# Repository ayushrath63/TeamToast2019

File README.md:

Team Toast - Micromouse 2018-2019
======
Created by Ayush Rath and Emily Chen

Hardware (PCB) and software used to build and program a Micromouse robot

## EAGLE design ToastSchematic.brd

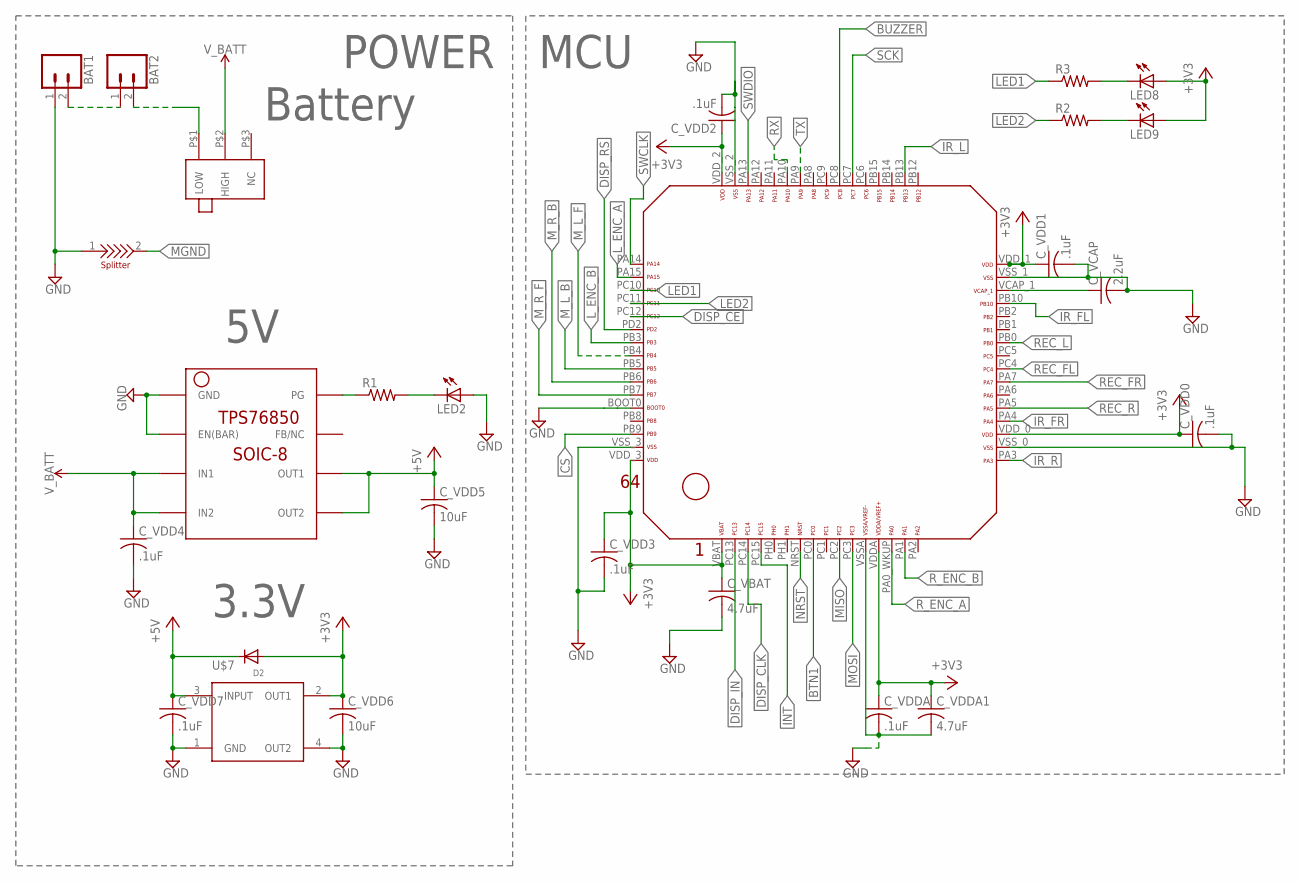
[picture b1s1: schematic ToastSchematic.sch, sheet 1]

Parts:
BAT1, BAT2: CONN_02JST-PTH-2; JST-2-PTH
C_VBAT: 4.7uF; C0603
C_VCAP: 2.2uF; C0603
C_VDD0, C_VDD1, C_VDD2, C_VDD3, C_VDD4, C_VDD7: .1uF; C0603
C_VDD5, C_VDD6: 10uF; C0603
C_VDDA: .1uF; C0603
C_VDDA1: 4.7uF; C0603
D2: DIODESOD-323F; SOD-323F
LED2, LED8, LED9: LEDCHIPLED_0603; CHIPLED_0603
R1, R2, R3: R-US_R0603; R0603
U$1: STM32F411/446_LQFP64
U$2: GH39P0
U$3: TPS76850(SOIC-8)
U$7: TLV1117; SOT-223
U$9: SPLITTER

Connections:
+3V3: C_VBAT.1, C_VDD0.1, C_VDD1.1, C_VDD2.1, C_VDD3.1, C_VDD6.1, C_VDDA.1, C_VDDA1.1, D2.A, LED8.A, LED9.A, U$1.VBAT, U$1.VDDA, U$1.VDD_0, U$1.VDD_1, U$1.VDD_2, U$1.VDD_3, U$7.2 (OUT1); also elsewhere on the board
+5V: C_VDD5.1, C_VDD7.1, D2.C, U$3.OUT1, U$3.OUT2, U$7.3 (INPUT); also elsewhere on the board
BTN1: U$1.PC0; also elsewhere on the board
BUZZER: U$1.PC8; also elsewhere on the board
CS: U$1.PB9; also elsewhere on the board
DISP_CE: U$1.PC12; also elsewhere on the board
DISP_CLK: U$1.PC14; also elsewhere on the board
DISP_IN: U$1.PC13; also elsewhere on the board
DISP_RS: U$1.PD2; also elsewhere on the board
GND: BAT1.1, C_VBAT.2, C_VCAP.2, C_VDD0.2, C_VDD1.2, C_VDD2.2, C_VDD3.2, C_VDD4.2, C_VDD5.2, C_VDD6.2, C_VDD7.2, C_VDDA.2, C_VDDA1.2, LED2.A, U$1.BOOT0, U$1.VSSA, U$1.VSS_0, U$1.VSS_1, U$1.VSS_2, U$1.VSS_3, U$3.EN(BAR), U$3.GND, U$7.1 (GND), U$7.4 (OUT2), U$9.1; also elsewhere on the board
INT: U$1.PC15; also elsewhere on the board
IR_FL: U$1.PB10; also elsewhere on the board
IR_FR: U$1.PA4; also elsewhere on the board
IR_L: U$1.PB13; also elsewhere on the board
IR_R: U$1.PA3; also elsewhere on the board
LED1: R3.1, U$1.PC10
LED2: R2.1, U$1.PC11
L_ENC_A: U$1.PA15; also elsewhere on the board
L_ENC_B: U$1.PB3; also elsewhere on the board
MGND: U$9.2; also elsewhere on the board
MISO: U$1.PC2; also elsewhere on the board
MOSI: U$1.PC3; also elsewhere on the board
M_L_B: U$1.PB5; also elsewhere on the board
M_L_F: U$1.PB4; also elsewhere on the board
M_R_B: U$1.PB6; also elsewhere on the board
M_R_F: U$1.PB7; also elsewhere on the board
unnamed: BAT1.2, BAT2.1
unnamed: BAT2.2, U$2.P$1 (LOW)
unnamed: C_VCAP.1, U$1.VCAP_1
unnamed: LED8.C, R3.2
unnamed: LED2.C, R1.2
unnamed: R1.1, U$3.PG
unnamed: LED9.C, R2.2
NRST: U$1.NRST; also elsewhere on the board
REC_FL: U$1.PC4; also elsewhere on the board
REC_FR: U$1.PA7; also elsewhere on the board
REC_L: U$1.PB0; also elsewhere on the board
REC_R: U$1.PA5; also elsewhere on the board
RX: U$1.PA10; also elsewhere on the board
R_ENC_A: U$1.PA0_WKUP (PA0_AKUP); also elsewhere on the board
R_ENC_B: U$1.PA1; also elsewhere on the board
SCK: U$1.PC7; also elsewhere on the board
SWCLK: U$1.PA14; also elsewhere on the board
SWDIO: U$1.PA13; also elsewhere on the board
TX: U$1.PA9; also elsewhere on the board
V_BATT: C_VDD4.1, U$2.P$2 (HIGH), U$3.IN1, U$3.IN2; also elsewhere on the board

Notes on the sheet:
MCU
POWER
3.3V
Battery

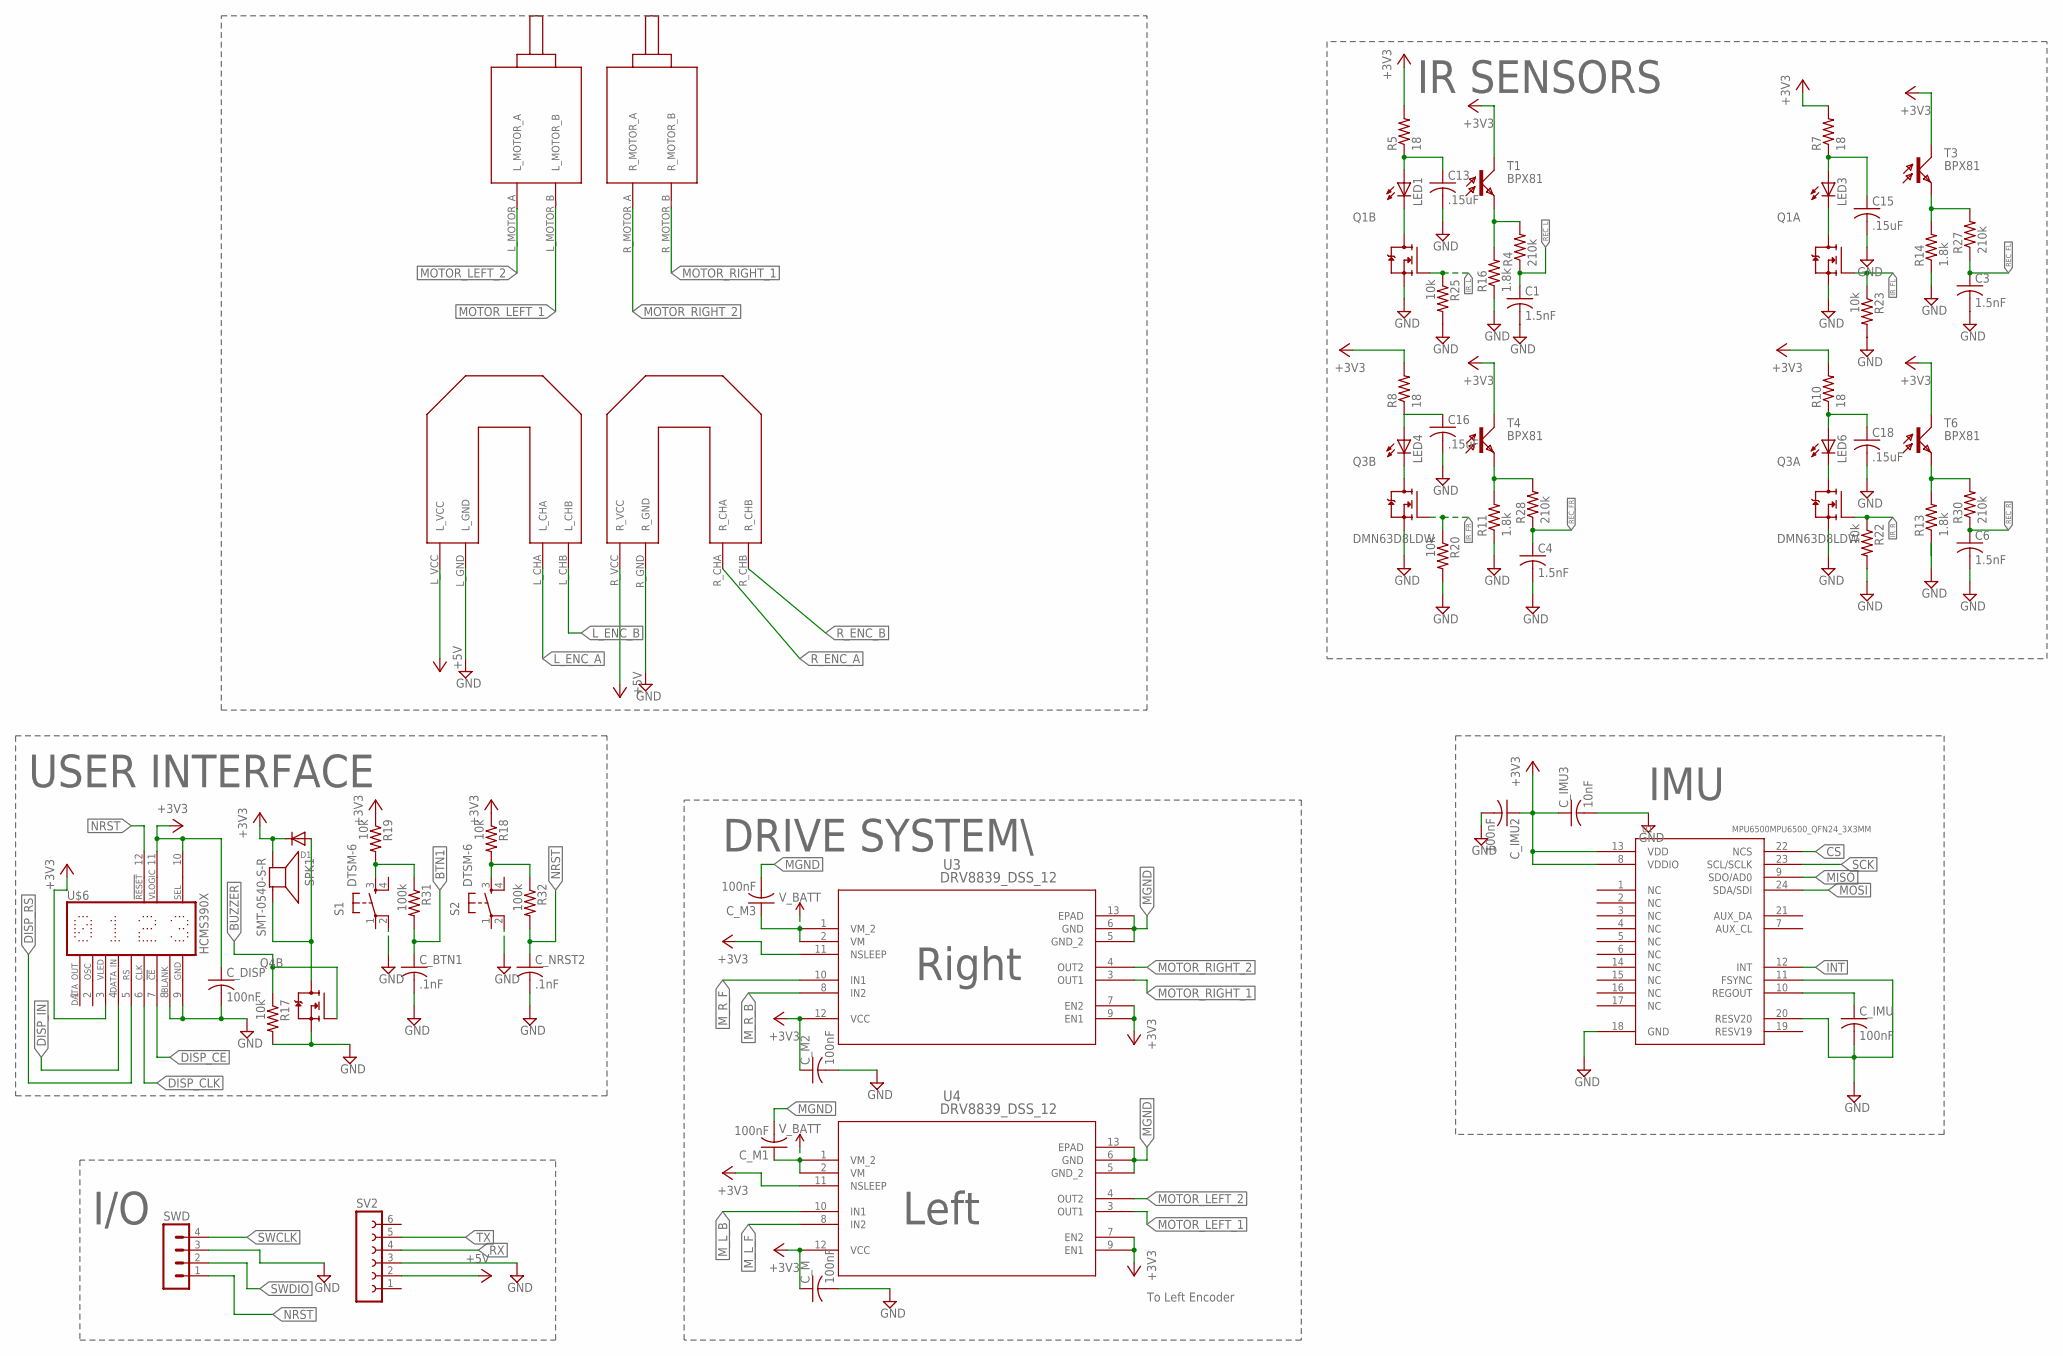
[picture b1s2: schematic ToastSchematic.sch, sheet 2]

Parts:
C1, C3, C4, C6: 1.5nF; C0603K
C13, C15, C16, C18: .15uF; C0603K
C_BTN1: .1nF; C0603K
C_DISP: 100nF; C0603K
C_IMU, C_IMU2: 100nF; C0603K
C_IMU3: 10nF; C0603K
C_M, C_M1, C_M2, C_M3: 100nF; C0603K
C_NRST2: .1nF; C0603K
D1: DIODESOD-323F; SOD-323F
LED1, LED3, LED4, LED6: LED5MM
Q1, Q3, Q4: DMN63D8LDW; SOT363
R4, R27, R28, R30: 210k; R0603
R5, R7, R8, R10: 18; R0603
R11, R13, R14, R16: 1.8k; R0603
R17, R18, R19, R20, R22, R23, R25: 10k; R0603
R31, R32: 100k; R0603
S1, S2: DTSM-6
SPK1: SMT-0540-S-R
SV2: FE06-1; FE06
SWD: MA04-1
T1, T3, T4, T6: BPX81
U1: MPU6500MPU6500_QFN24_3X3MM; QFN24_3X3MM
U3, U4: DRV8839_DSS_12; DSS12_P9X2
U$4: FUTURA_V1.0_MOTOR_MOUNT; FUTURA_V1.0_MOTOT_MOUNT
U$6: HCMS390X

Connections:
+3V3: C_DISP.1, C_IMU2.1, C_IMU3.1, C_M.1, C_M2.1, D1.C, R5.2, R7.2, R8.2, R10.2, R18.1, R19.1, SPK1.- (+), T1.C, T3.C, T4.C, T6.C, U1.8 (VDDIO), U1.13 (VDD), U3.7 (EN2), U3.9 (EN1), U3.11 (NSLEEP), U3.12 (VCC), U4.7 (EN2), U4.9 (EN1), U4.11 (NSLEEP), U4.12 (VCC), U$6.3 (VLED), U$6.10 (SEL), U$6.11 (VLOGIC); also elsewhere on the board
+5V: SV2.2, U$4.L_VCC, U$4.R_VCC; also elsewhere on the board
BTN1: C_BTN1.1, R31.2; also elsewhere on the board
BUZZER: Q4.5 (G), R17.1; also elsewhere on the board
CS: U1.22 (NCS); also elsewhere on the board
DISP_CE: U$6.7 (!CE); also elsewhere on the board
DISP_CLK: U$6.6 (CLK); also elsewhere on the board
DISP_IN: U$6.4 (IN); also elsewhere on the board
DISP_RS: U$6.5 (RS); also elsewhere on the board
GND: C1.2, C3.2, C4.2, C6.2, C13.2, C15.2, C16.2, C18.2, C_BTN1.2, C_DISP.2, C_IMU.2, C_IMU2.2, C_IMU3.2, C_M.2, C_M2.2, C_NRST2.2, Q1.1 (S), Q1.4 (S), Q3.1 (S), Q3.4 (S), Q4.4 (S), R11.1, R13.1, R14.1, R16.1, R17.2, R20.2, R22.2, R23.2, R25.2, S1.2, S2.2, SV2.3, SWD.3, U1.11 (FSYNC), U1.18 (GND), U1.20 (RESV20), U$4.L_GND, U$4.R_GND, U$6.8 (BLANK), U$6.9 (GND); also elsewhere on the board
INT: U1.12 (INT); also elsewhere on the board
IR_FL: Q1.2 (G), R23.1; also elsewhere on the board
IR_FR: Q3.5 (G), R20.1; also elsewhere on the board
IR_L: Q1.5 (G), R25.1; also elsewhere on the board
IR_R: Q3.2 (G), R22.1; also elsewhere on the board
L_ENC_A: U$4.L_CHA; also elsewhere on the board
L_ENC_B: U$4.L_CHB; also elsewhere on the board
MGND: C_M1.2, C_M3.2, U3.5 (GND_2), U3.6 (GND), U3.13 (EPAD), U4.5 (GND_2), U4.6 (GND), U4.13 (EPAD); also elsewhere on the board
MISO: U1.9 (SDO/AD0); also elsewhere on the board
MOSI: U1.24 (SDA/SDI); also elsewhere on the board
MOTOR_LEFT_1: U4.3 (OUT1), U$4.L_MOTOR_B
MOTOR_LEFT_2: U4.4 (OUT2), U$4.L_MOTOR_A
MOTOR_RIGHT_1: U3.3 (OUT1), U$4.R_MOTOR_B
MOTOR_RIGHT_2: U3.4 (OUT2), U$4.R_MOTOR_A
M_L_B: U4.10 (IN1); also elsewhere on the board
M_L_F: U4.8 (IN2); also elsewhere on the board
M_R_B: U3.8 (IN2); also elsewhere on the board
M_R_F: U3.10 (IN1); also elsewhere on the board
unnamed: C13.1, LED1.A, R5.1
unnamed: LED1.K (C), Q1.3 (D)
unnamed: R19.2, R31.1, S1.3
unnamed: LED3.K (C), Q1.6 (D)
unnamed: R18.2, R32.1, S2.3
unnamed: C18.1, LED6.A, R10.1
unnamed: LED6.K (C), Q3.6 (D)
unnamed: C16.1, LED4.A, R8.1
unnamed: C_IMU.1, U1.10 (REGOUT)
unnamed: LED4.K (C), Q3.3 (D)
unnamed: D1.A, Q4.3 (D), SPK1.+ (-)
unnamed: R4.2, R16.2, T1.E
unnamed: R14.2, R27.2, T3.E
unnamed: R11.2, R28.2, T4.E
unnamed: R13.2, R30.2, T6.E
unnamed: C15.1, LED3.A, R7.1
NRST: C_NRST2.1, R32.2, SWD.1, U$6.12 (NOT_RESET); also elsewhere on the board
REC_FL: C3.1, R27.1; also elsewhere on the board
REC_FR: C4.1, R28.1; also elsewhere on the board
REC_L: C1.1, R4.1; also elsewhere on the board
REC_R: C6.1, R30.1; also elsewhere on the board
RX: SV2.4; also elsewhere on the board
R_ENC_A: U$4.R_CHA; also elsewhere on the board
R_ENC_B: U$4.R_CHB; also elsewhere on the board
SCK: U1.23 (SCL/SCLK); also elsewhere on the board
SWCLK: SWD.4; also elsewhere on the board
SWDIO: SWD.2; also elsewhere on the board
TX: SV2.5; also elsewhere on the board
V_BATT: C_M1.1, C_M3.1, U3.1 (VM_2), U3.2 (VM), U4.1 (VM_2), U4.2 (VM); also elsewhere on the board

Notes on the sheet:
DRIVE SYSTEM\
Right
Left
USER INTERFACE
IR SENSORS
IMU
I/O
To Left Encoder

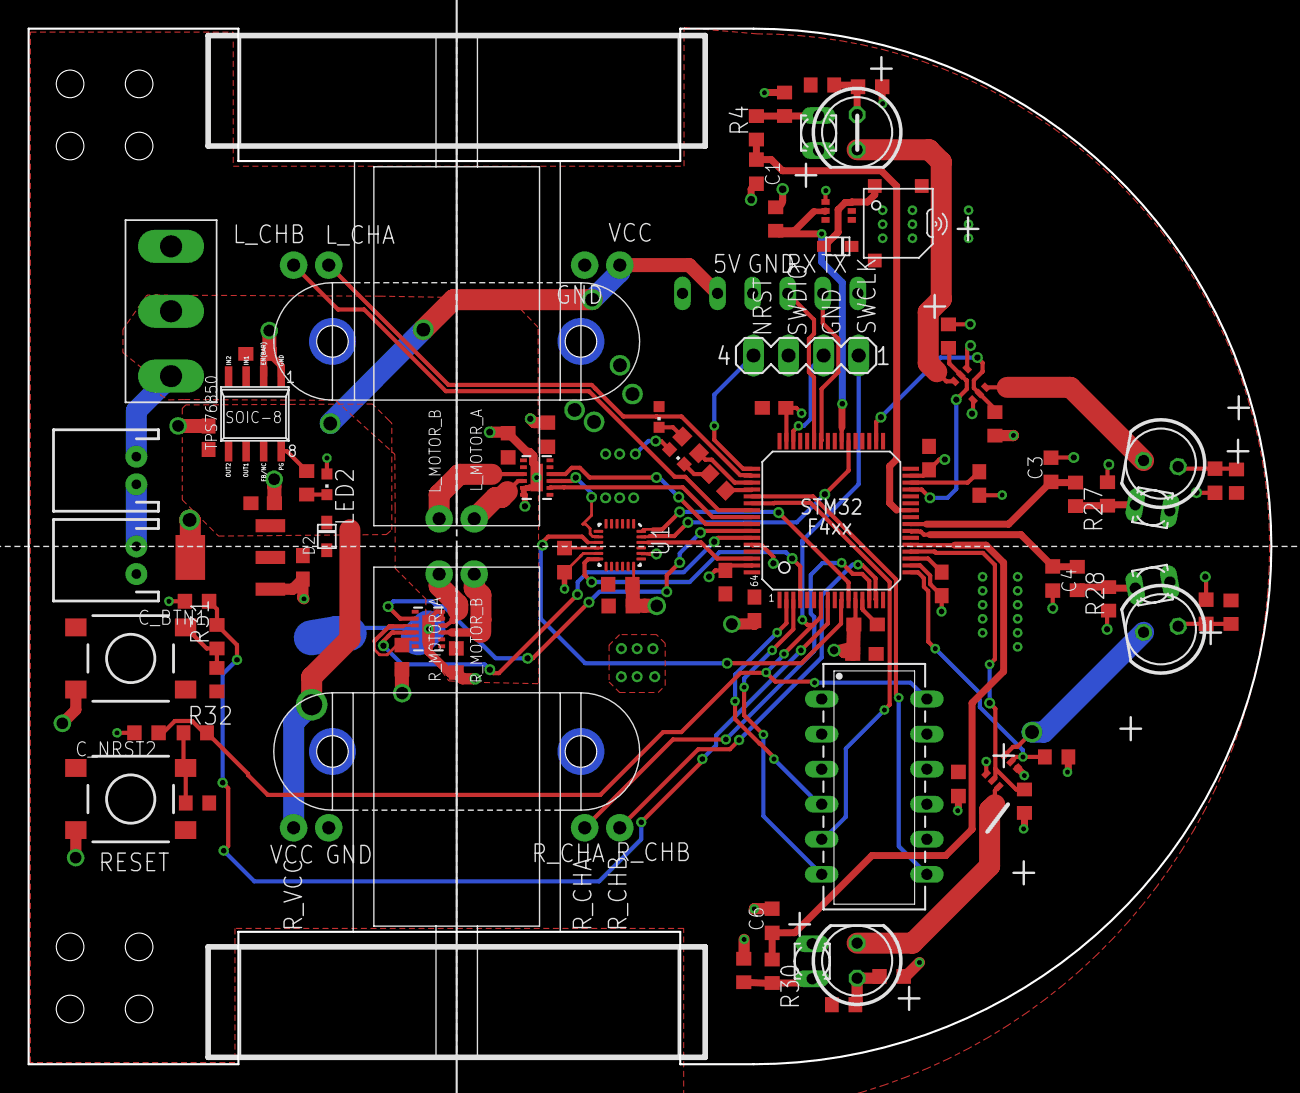
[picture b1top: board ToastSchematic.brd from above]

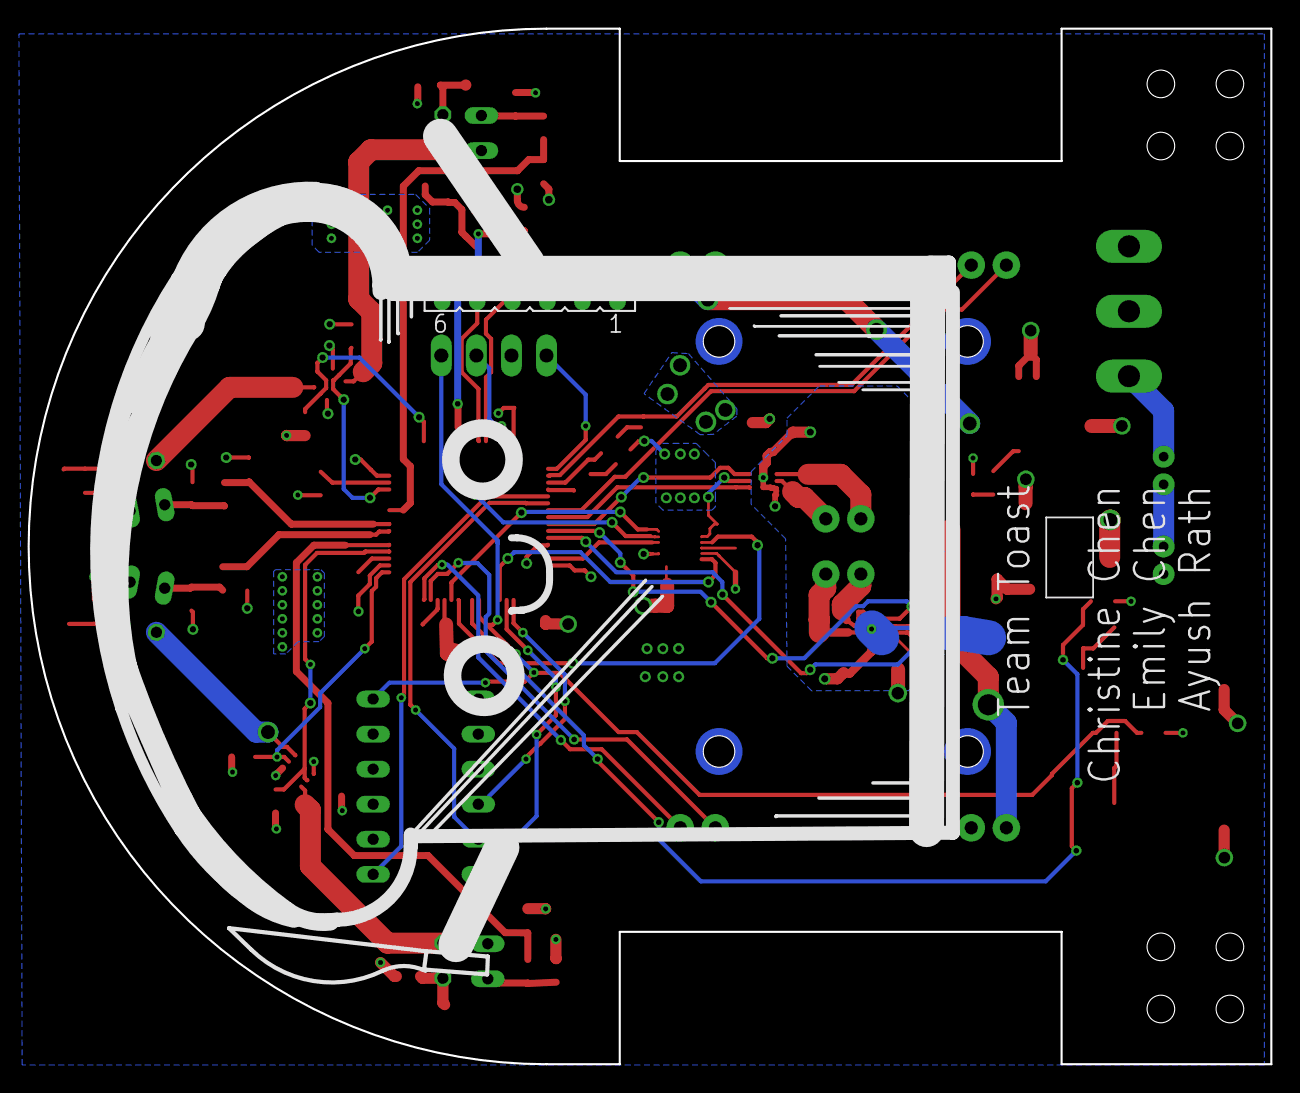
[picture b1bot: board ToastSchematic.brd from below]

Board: 2 copper layers, 90.0 x 75.0 mm, 87 parts (2 on the bottom side), 66 nets.

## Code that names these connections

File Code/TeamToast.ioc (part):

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Mcu.Name=STM32F411R(C-E)Tx
Mcu.Package=LQFP64
Mcu.UserName=STM32F411RETx
PA0-WKUP.GPIOParameters=GPIO_PuPd,GPIO_Label
PA0-WKUP.GPIO_Label=R_Encoder_A
PA0-WKUP.GPIO_PuPd=GPIO_PULLUP
PA0-WKUP.Signal=S_TIM5_CH1
PA1.GPIOParameters=GPIO_PuPd,GPIO_Label
PA1.GPIO_Label=R_Encoder_B
PA1.GPIO_PuPd=GPIO_PULLUP
PA1.Signal=S_TIM5_CH2
PA10.Mode=Asynchronous
PA10.Signal=USART1_RX
PA13.Mode=Serial_Wire
PA13.Signal=SYS_JTMS-SWDIO
PA14.Mode=Serial_Wire
PA14.Signal=SYS_JTCK-SWCLK
PA15.GPIOParameters=GPIO_PuPd,GPIO_Label
PA15.GPIO_Label=L_Encoder_A
PA15.GPIO_PuPd=GPIO_PULLUP
PA15.Signal=S_TIM2_CH1_ETR
PA3.GPIOParameters=GPIO_Label
PA3.GPIO_Label=IR_R
PA3.Signal=GPIO_Output
PA4.GPIOParameters=GPIO_Label
PA4.GPIO_Label=IR_FR
PA4.Signal=GPIO_Output
PA5.GPIOParameters=GPIO_Label
PA5.GPIO_Label=Rec_R
PA5.Signal=ADCx_IN5
PA7.GPIOParameters=GPIO_Label
PA7.GPIO_Label=Rec_FR
PA7.Signal=ADCx_IN7
PA9.Mode=Asynchronous
PA9.Signal=USART1_TX
PB0.GPIOParameters=GPIO_Label
PB0.GPIO_Label=Rec_L
PB0.Signal=ADCx_IN8
PB10.GPIOParameters=GPIO_Label
PB10.GPIO_Label=IR_FL
PB10.Signal=GPIO_Output
PB13.GPIOParameters=GPIO_Label
PB13.GPIO_Label=IR_L
PB13.Signal=GPIO_Output
PB3.GPIOParameters=GPIO_PuPd,GPIO_Label
PB3.GPIO_Label=L_Encoder_B
PB3.GPIO_PuPd=GPIO_PULLUP
PB3.Signal=S_TIM2_CH2
PB4.GPIOParameters=GPIO_Label
PB4.GPIO_Label=Motor_L_F
PB4.Signal=S_TIM3_CH1
PB5.GPIOParameters=GPIO_Label
PB5.GPIO_Label=Motor_L_B
PB5.Signal=S_TIM3_CH2
PB6.GPIOParameters=GPIO_Label
PB6.GPIO_Label=Motor_R_B
PB6.Signal=S_TIM4_CH1
PB7.GPIOParameters=GPIO_Label
PB7.GPIO_Label=Motor_R_F
PB7.Signal=S_TIM4_CH2
PB9.GPIOParameters=GPIO_Label
PB9.GPIO_Label=IMU_nCS
PB9.Signal=GPIO_Output
PC0.GPIOParameters=GPIO_Label
PC0.GPIO_Label=Btn1
PC0.Signal=GPIO_Input
PC10.GPIOParameters=GPIO_Label
PC10.GPIO_Label=LED1
PC10.Signal=GPIO_Output
PC11.GPIOParameters=GPIO_Label
PC11.GPIO_Label=LED2
PC11.Signal=GPIO_Output
PC12.GPIOParameters=GPIO_Label
PC12.GPIO_Label=Disp_CE
PC12.Signal=GPIO_Output
PC13-ANTI_TAMP.GPIOParameters=GPIO_Label
PC13-ANTI_TAMP.GPIO_Label=Disp_In
PC13-ANTI_TAMP.Signal=GPIO_Output
PC14-OSC32_IN.GPIOParameters=GPIO_Label
PC14-OSC32_IN.GPIO_Label=Disp_Clk
PC14-OSC32_IN.Signal=GPIO_Output
PC15-OSC32_OUT.GPIOParameters=GPIO_Label
PC15-OSC32_OUT.GPIO_Label=IMU_Int
PC15-OSC32_OUT.Signal=GPIO_Input
PC2.GPIOParameters=GPIO_Label
PC2.GPIO_Label=IMU_MISO
PC2.Mode=Full_Duplex_Master
PC2.Signal=SPI2_MISO
PC3.GPIOParameters=GPIO_Label
PC3.GPIO_Label=IMU_MOSI
PC3.Mode=Full_Duplex_Master
PC3.Signal=SPI2_MOSI
PC4.GPIOParameters=GPIO_Label
PC4.GPIO_Label=Rec_FL
PC4.Signal=ADCx_IN14
PC7.Mode=Full_Duplex_Master
PC7.Signal=SPI2_SCK
PC8.GPIOParameters=GPIO_Label
PC8.GPIO_Label=Buzzer
PC8.Signal=GPIO_Output
PD2.GPIOParameters=GPIO_Label
PD2.GPIO_Label=Disp_RS
PD2.Signal=GPIO_Output
RCC.HSE_VALUE=25000000
RCC.SYSCLKFreq_VALUE=16000000
board=custom

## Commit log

2019-01-23 Add PCB
2019-01-23 Added Template Code
2019-01-23 Fix directory structure
2019-04-11 right encoder working
2019-04-11 clean
2019-04-11 encoder is kill
2019-04-25 Test gyro, working encoders, motors
2019-04-26 Working IMU, Motors, Encoders
2019-04-26 CXX HAL test
2019-04-26 update gitignore
2019-04-26 Convert all src files to .cpp
2019-05-01 ADC test
2019-05-02 IMU class cteated
2019-05-07 motor class added
2019-05-15 Testing motor
2019-05-15 Test IR Sensors
2019-05-16 IRsensor files
2019-05-16 Fix motors
2019-05-16 remove extra .ld
2019-05-16 add PID class
2019-05-22 PID value set
2019-05-23 useless drive class
2019-05-23 turn left then right
2019-05-23 Gyro PID turn
2019-05-23 rudimentary forward move
2019-05-25 Motion profile
2019-05-26 Add encoder angle PID
2019-05-26 Remove IR Delay
2019-05-26 Update IR
2019-05-26 update stuff
2019-05-26 changed sensor value
2019-05-26 kind of working code
2019-05-26 seperated IRsensor and Drive
2019-05-26 random kinda working code
2019-05-27 Add ETL support
2019-05-27 remove broken motion profile
2019-05-27 Add command queue
2019-05-27 Added buzzer feedback
2019-05-27 Fix PID stop conditions
2019-05-28 Update IR values, broke drive logic?
2019-05-28 Implement IR PID (untested
2019-05-28 Update IR constants again, drive logic still broken
2019-05-28 UCLA AAMC 2019
2019-05-28 bug fix
2019-05-29 fixing IR tunning
2019-05-29 Add new threshold for left wall
2019-05-29 Try new PID func
2019-05-30 fixed IR PID
2019-05-30 Working wall follower
2019-06-02 Straights are bad
2019-06-02 Fix Makefile header deps
2019-06-02 added all files
2019-06-02 buggy code with queue
2019-06-02 working floodfill
2019-06-02 prioritizing turning
2019-06-04 Final update :(

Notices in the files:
parts and their libraries:
SparkFun-Connectors: Licensing: Creative Commons ShareAlike 4.0 International - https://creativecommons.org/licenses/by-sa/4.0
